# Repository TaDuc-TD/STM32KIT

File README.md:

# STM32F401 Development Board

Bo mạch phát triển tùy chỉnh sử dụng vi điều khiển STM32F401, được thiết kế bằng phần mềm KiCad.

---

## 1. Tổng quan PCB

### Mô hình PCB 3D

### Ảnh bo mạch thực tế

---

## 2. Mô tả dự án

Dự án tập trung vào thiết kế sơ đồ nguyên lý (schematic) và thiết kế mạch in (PCB) cho một bo mạch phát triển dựa trên vi điều khiển STM32F401.

Bo mạch được phát triển nhằm phục vụ cho việc nghiên cứu hệ thống nhúng, phát triển firmware, giao tiếp ngoại vi, thử nghiệm phần cứng và xây dựng các ứng dụng điều khiển sử dụng vi điều khiển.

---

## 3. Tính năng chính

- Thiết kế schematic và PCB hoàn toàn tùy chỉnh.
- Sử dụng vi điều khiển dòng STM32F401.
- Thiết kế và đi dây PCB bằng KiCad.
- Kiểm tra mô hình 3D để đánh giá bố trí linh kiện và khả năng lắp ráp cơ khí.

---

## 4. Thông số phần cứng

| Thông số | Giá trị |
| :--- | :--- |
| **Vi điều khiển** | STM32F401 Series |
| **Phần mềm thiết kế** | KiCad (Schematic Editor, PCB Editor, 3D Viewer) |
| **Nguồn cấp** | 5V DC |
| **Kích thước PCB** | 100 mm × 100 mm |
| **Số lớp PCB** | 2 lớp |
| **Giao tiếp ngoại vi** | 1× RS232 (MAX3232), 1× RS485 (MAX3485), 1× Ethernet (W5500) |
| **I/O & Ngoại vi khác** | 2× ADC, 4× Button, 5× LED |

---

## 5. Quy trình thiết kế

1. Thiết kế sơ đồ nguyên lý (Schematic).
2. Lựa chọn linh kiện và gán footprint.
3. Bố trí linh kiện và đi dây PCB.
4. Kiểm tra quy tắc thiết kế (DRC).

---

## 6. Công cụ sử dụng

- **KiCad**: Thiết kế nguyên lý, PCB, quản lý footprint và kiểm tra mô hình 3D.
- **Git**: Quản lý phiên bản mã nguồn cục bộ.
- **GitHub**: Lưu trữ mã nguồn và tài liệu dự án trực tuyến.

---

## 7. Cấu trúc Repository

```text
├── *.kicad_pro    # Tệp cấu hình dự án KiCad
├── *.kicad_sch    # Thiết kế sơ đồ nguyên lý
├── *.kicad_pcb    # Thiết kế mạch in PCB
└── images/        # Hình ảnh thực tế và ảnh render 3D

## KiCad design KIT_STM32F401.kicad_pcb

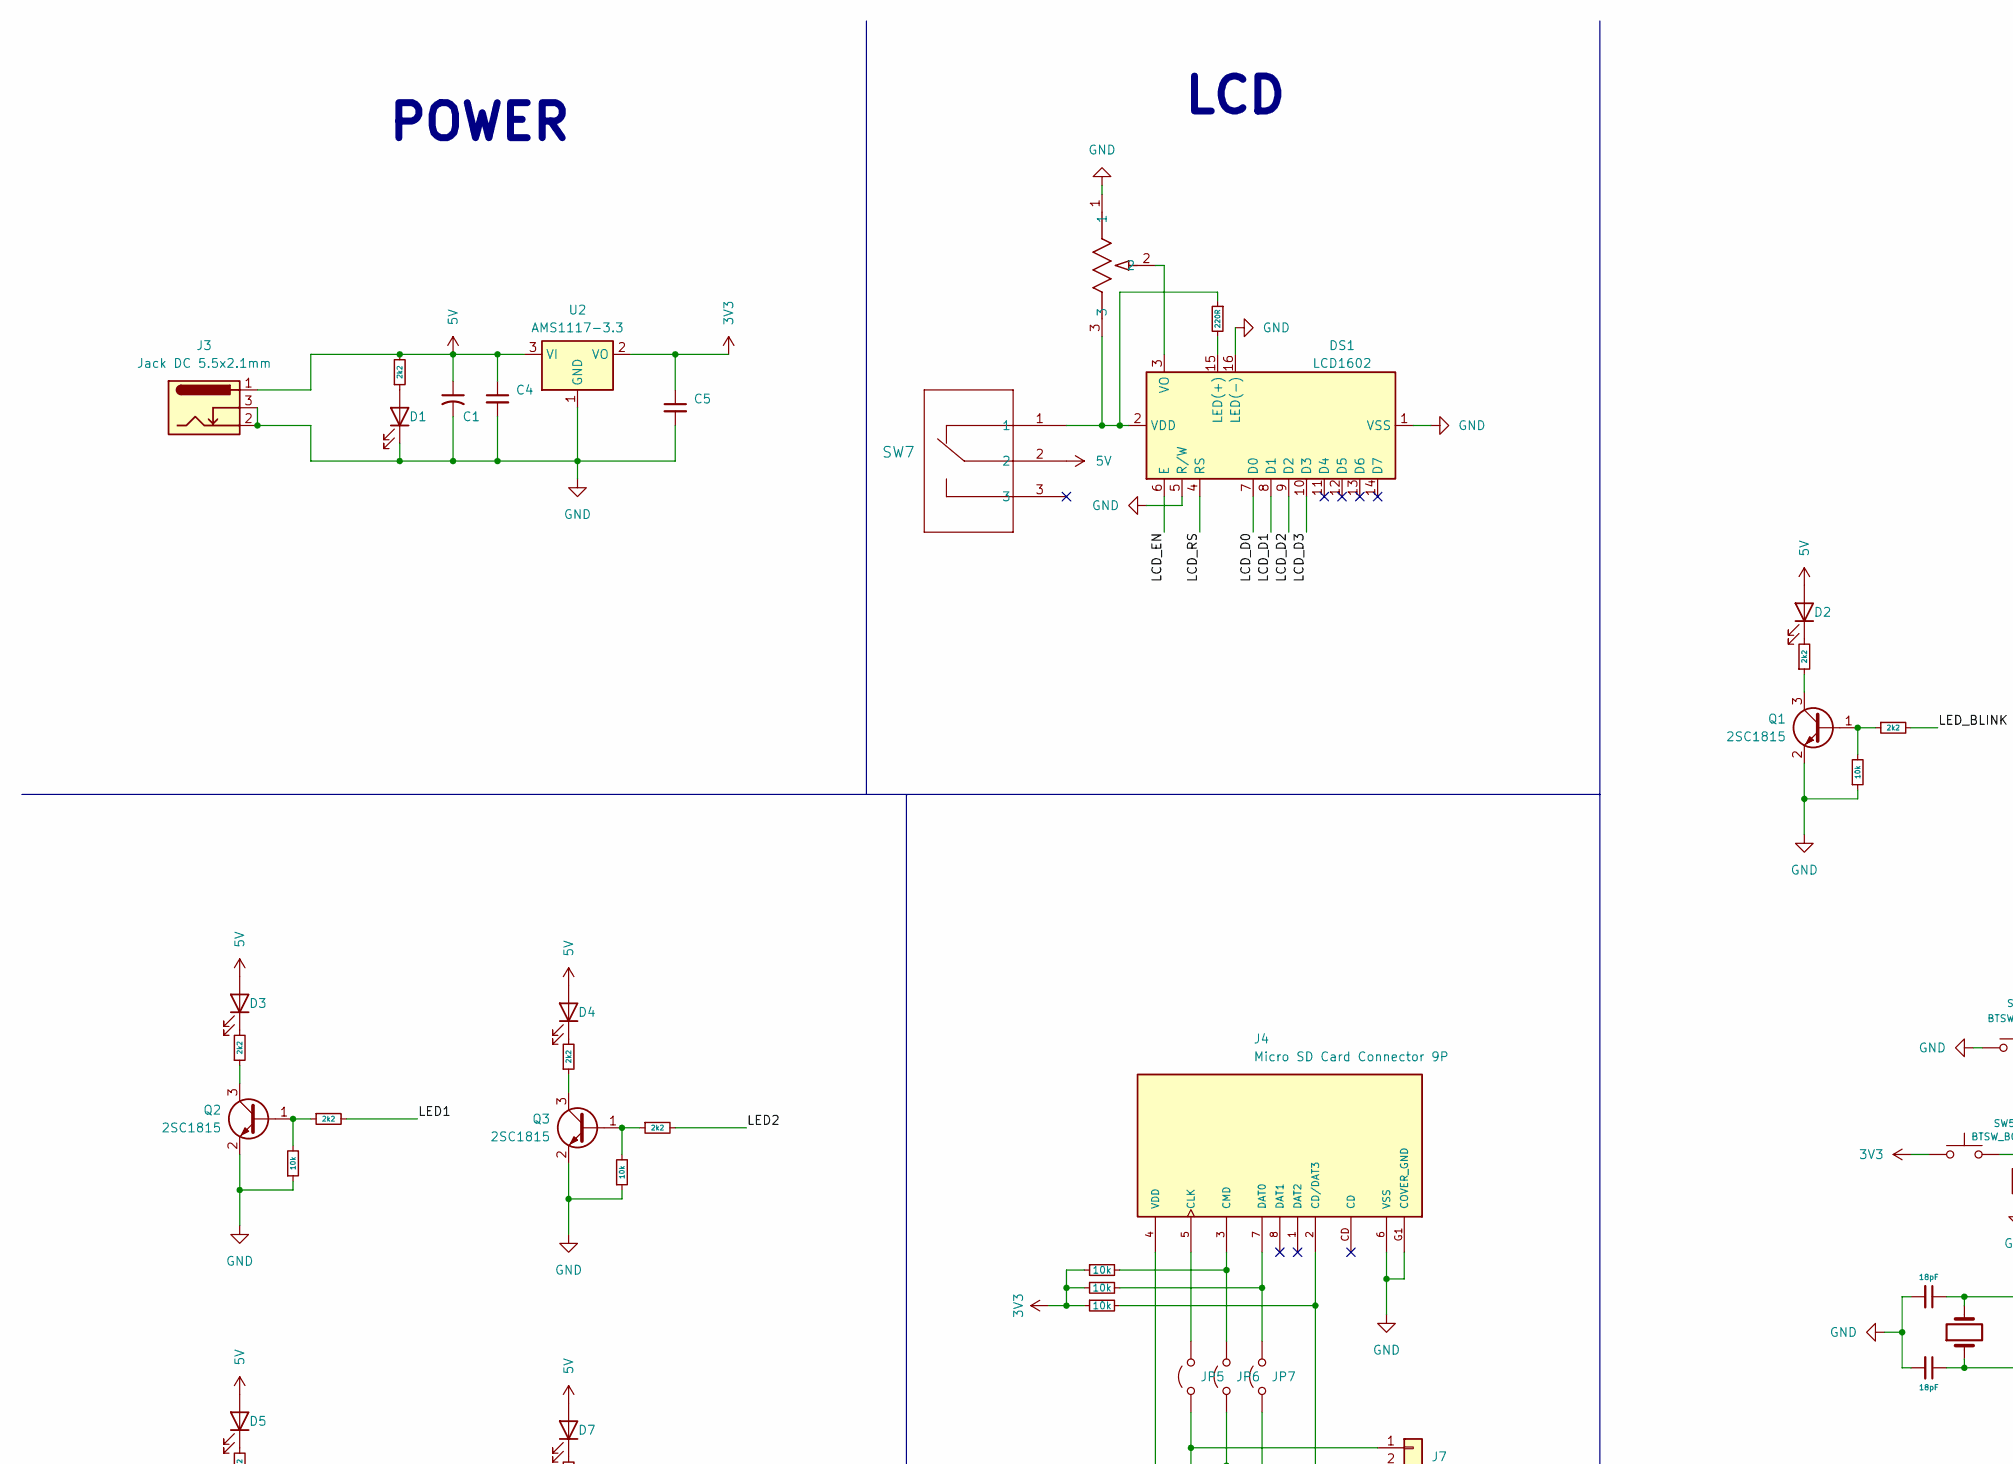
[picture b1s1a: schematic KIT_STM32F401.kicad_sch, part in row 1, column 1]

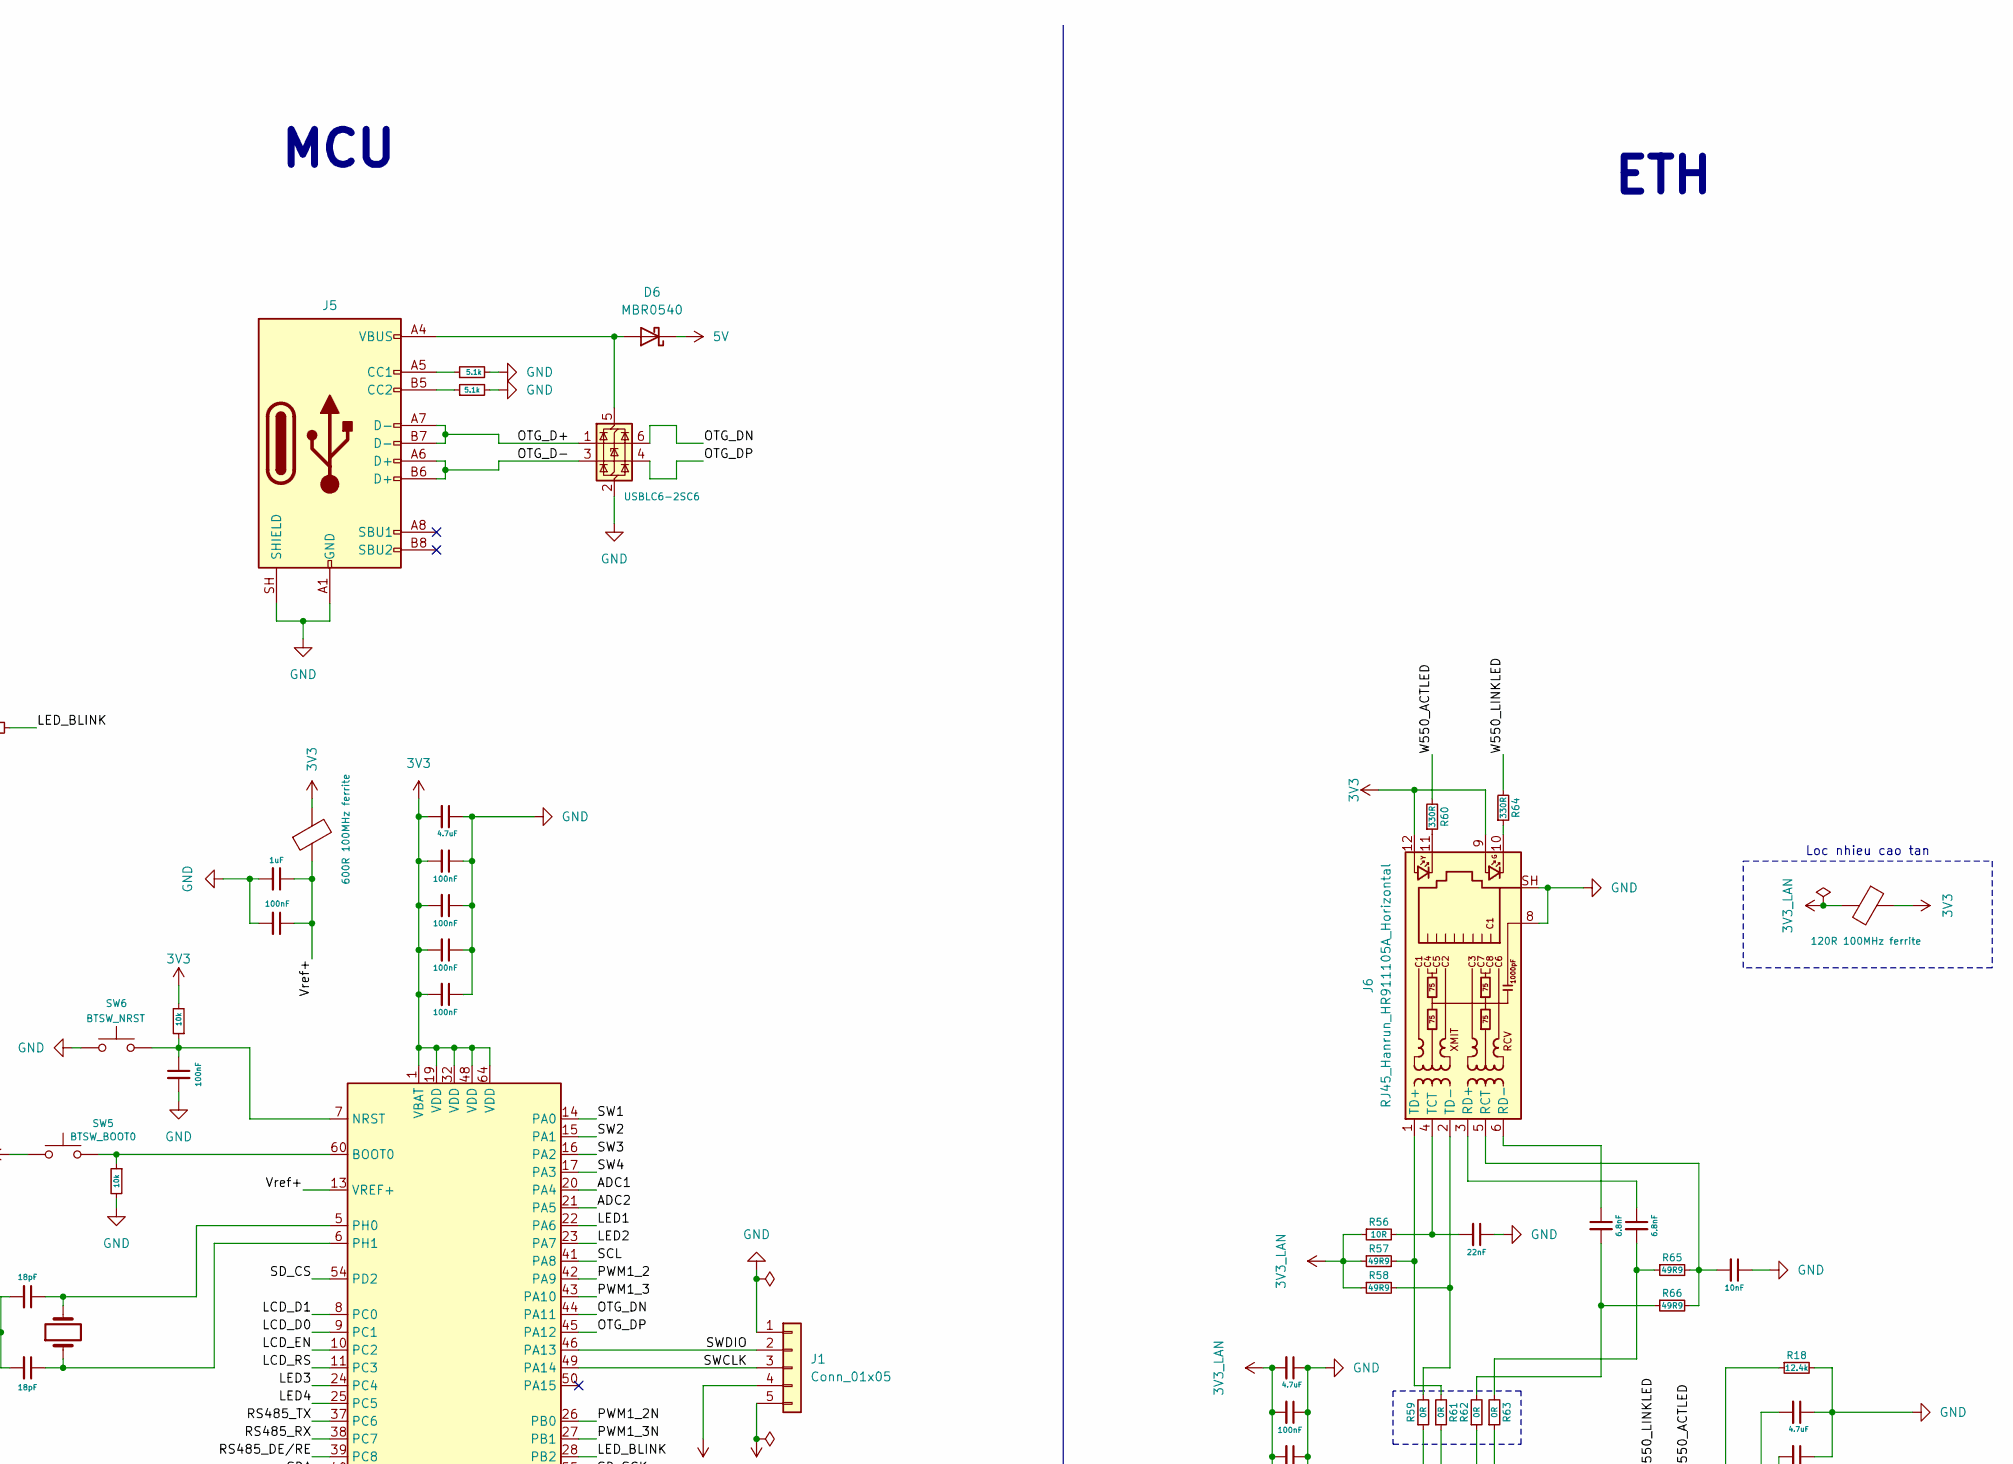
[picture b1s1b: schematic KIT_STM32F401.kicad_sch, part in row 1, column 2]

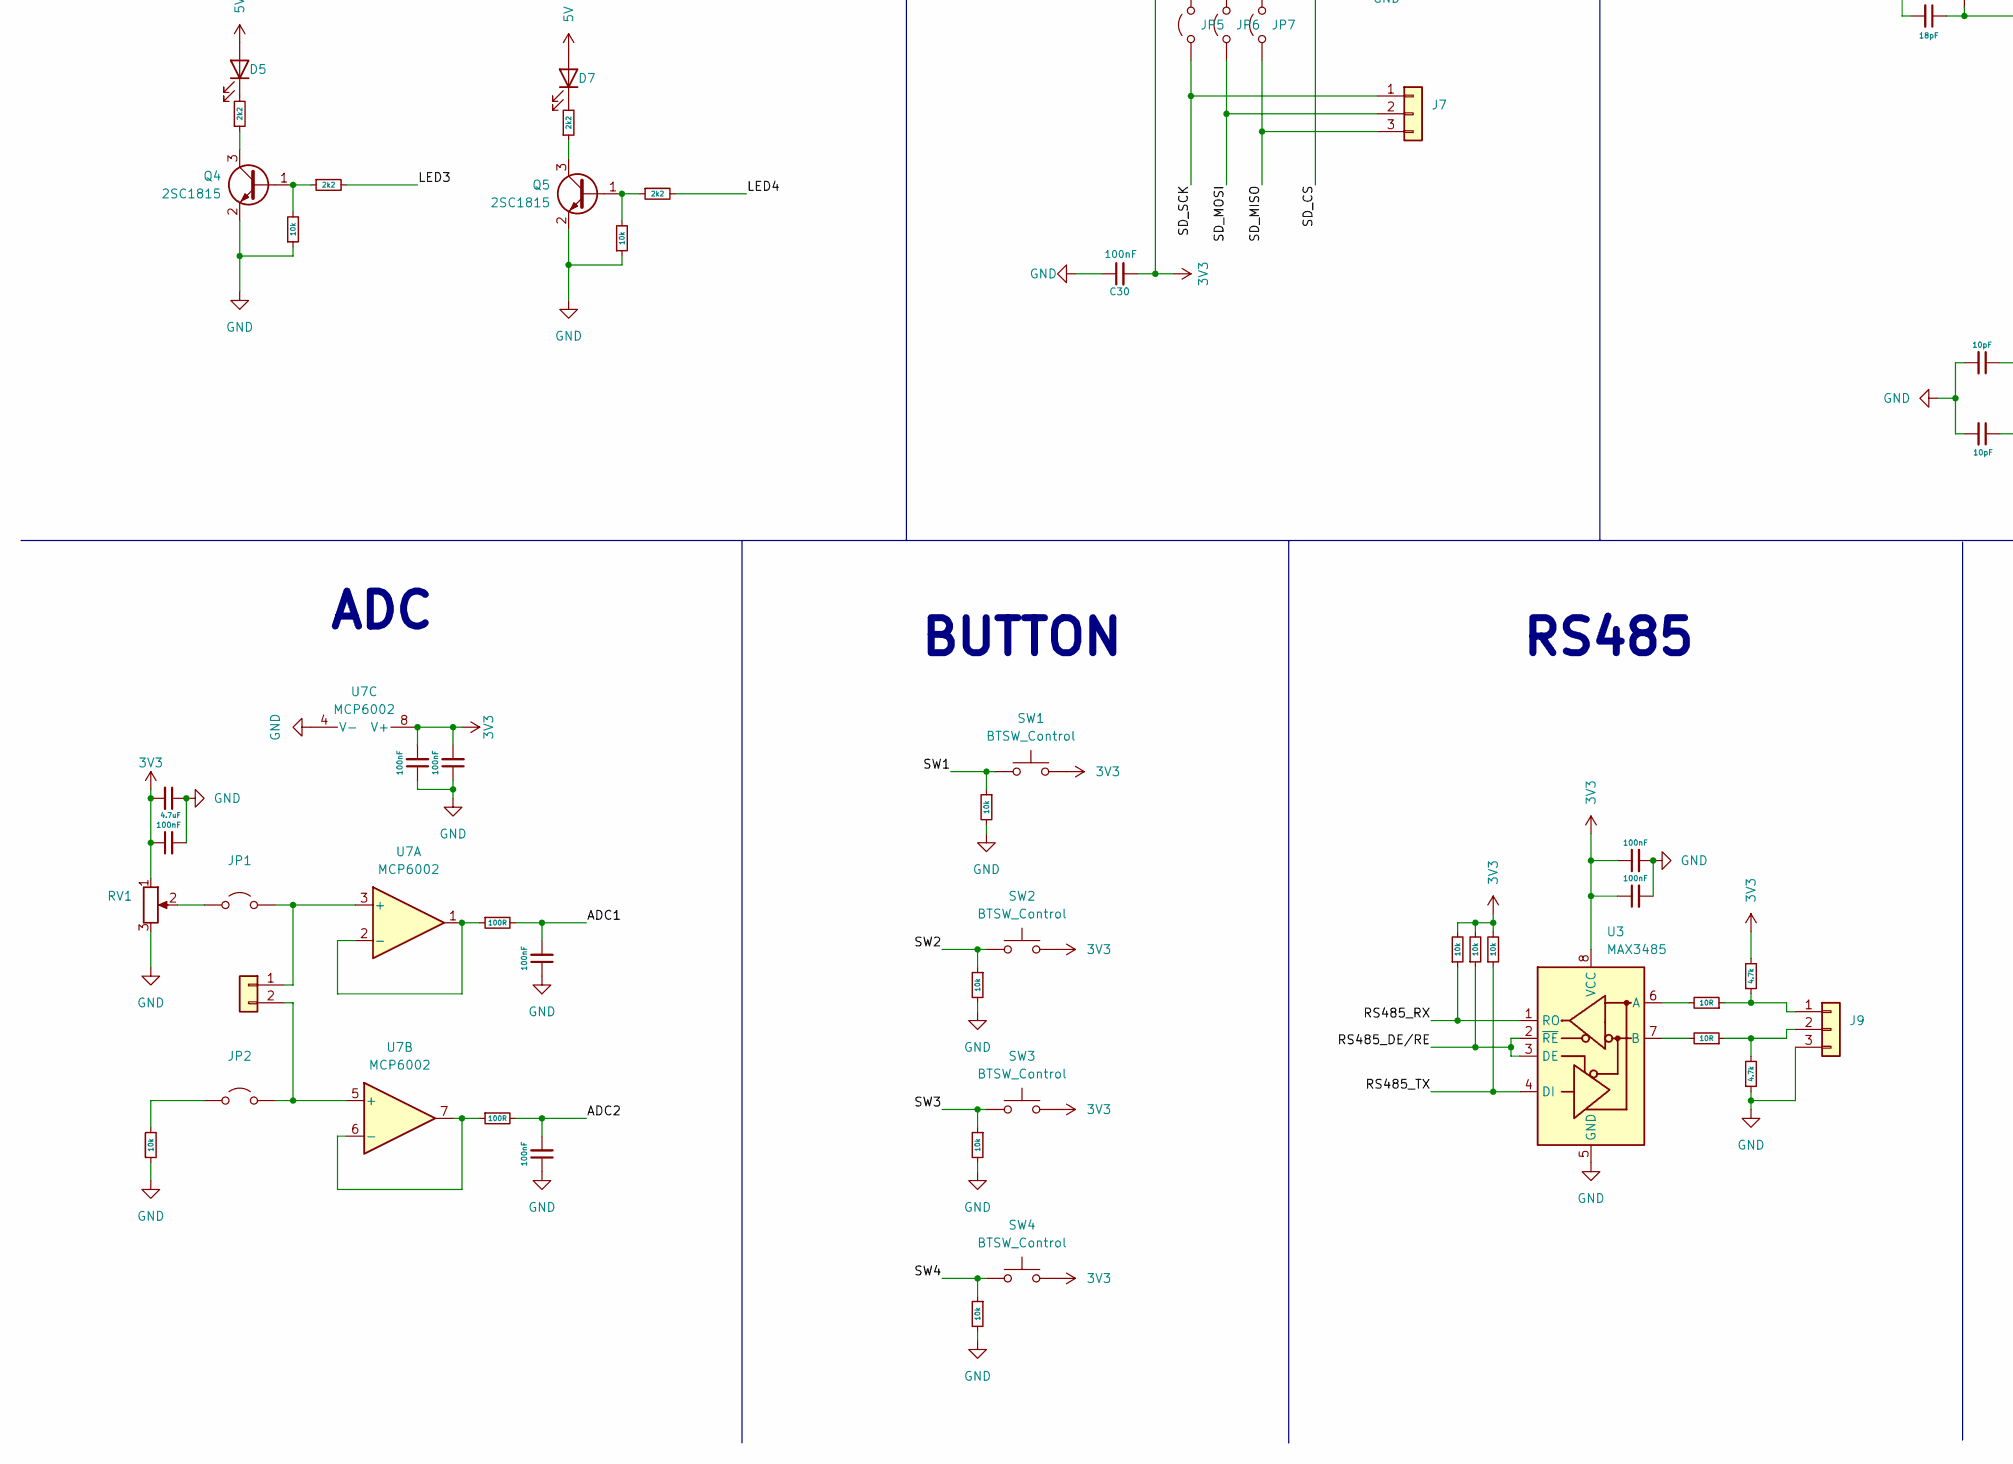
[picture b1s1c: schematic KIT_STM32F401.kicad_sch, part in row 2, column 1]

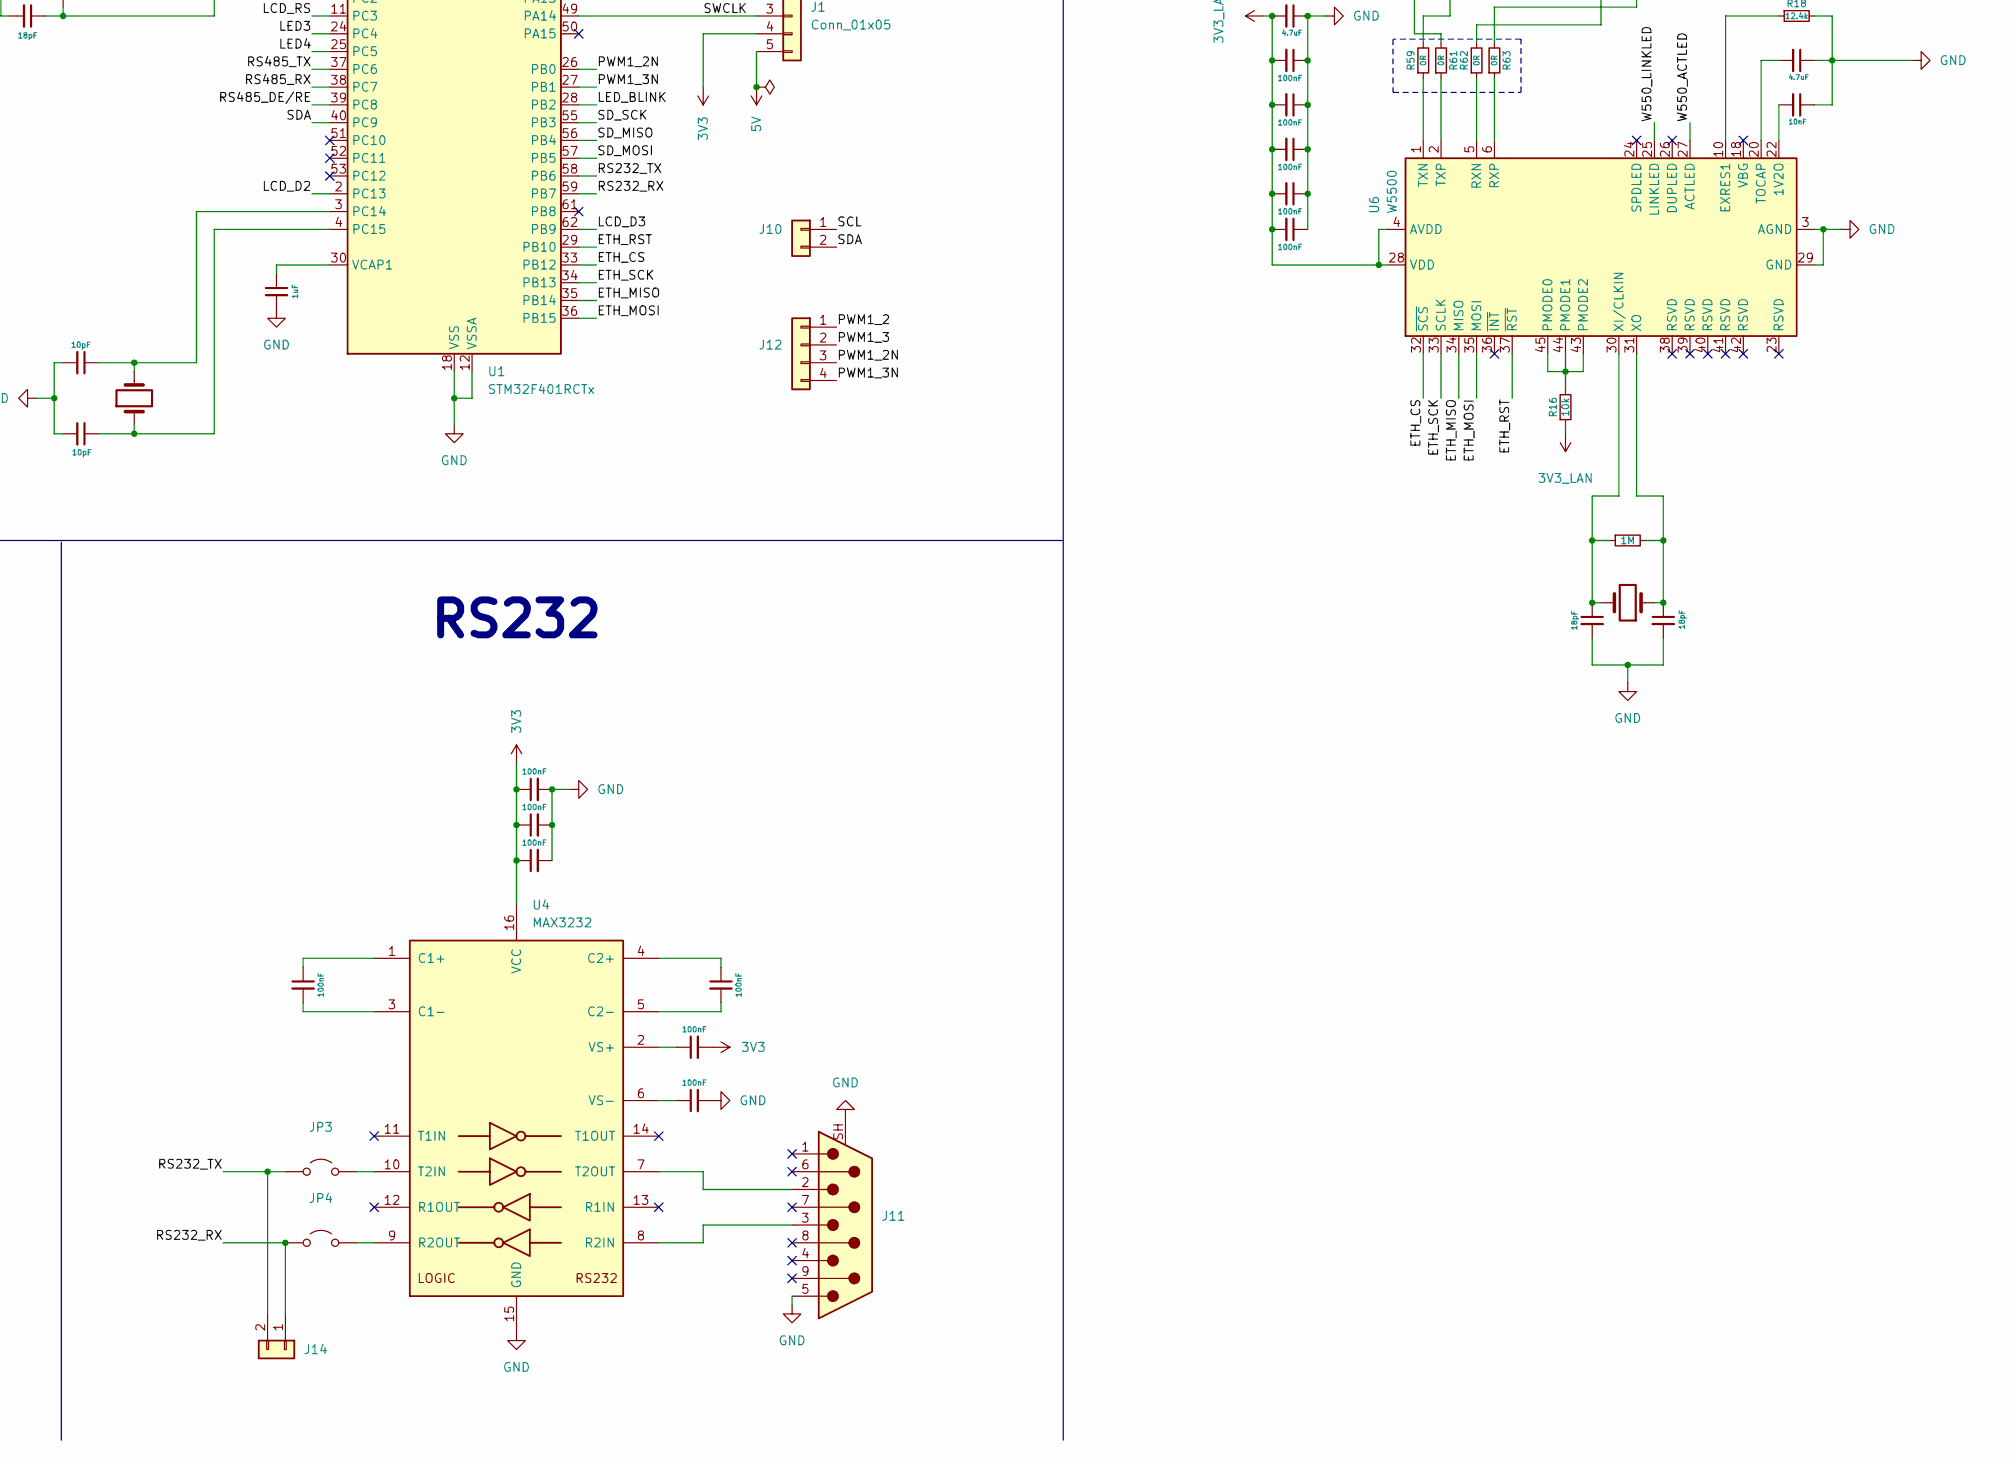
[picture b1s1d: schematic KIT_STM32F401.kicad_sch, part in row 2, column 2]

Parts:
C1: 220uF; CP_Elec_10x10
C4, C30, C33, C35, C36, C37, C38, C39, C42, C43, C44, C45, C46, C47, C48, C49, C50, C51, C52, C53, C54, C56, C57, C58, C59, C69, C70: 100nF; C_0603_1608Metric
C5, C34, C55, C67, C71: 4.7uF; C_1206_3216Metric
C24, C25, C62, C65: 18pF; C_0603_1608Metric
C31, C32: 10pF; C_0603_1608Metric
C40, C41: 1uF; C_1206_3216Metric
C61: 22nF; C_0603_1608Metric
C63, C64: 6.8nF; C_0603_1608Metric
C66, C68: 10nF; C_0603_1608Metric
D1, D2, D3, D4, D5, D7: LED; LED_1206_3216Metric
D6: MBR0540; D_SOD-123
DS1: LCD1602; WC1602A
FB2: 600R 100MHz ferrite; L_0603_1608Metric
FB3: 120R 100MHz ferrite; L_0603_1608Metric
J1: Conn_01x05; PinHeader_1x05_P2.54mm_Vertical
J3: Jack DC 5.5x2.1mm; BarrelJack_GCT_DCJ200-10-A_Horizontal
J4: Micro SD Card Connector 9P; CUI_MSD-4-A; PARTREV 1.0
J5: USB_C_USB2.0_16P; USB_C_Receptacle_GCT_USB4105-xx-A_16P_TopMnt_Horizontal
J6: RJ45_Hanrun_HR911105A_Horizontal
J7: Conn_01x03; PinHeader_1x03_P2.54mm_Vertical
J8: Conn_01x02; PhoenixContact_MSTBA_2,5_2-G-5,08_1x02_P5.08mm_Horizontal
J9: Conn_01x03; PhoenixContact_MSTBA_2,5_3-G-5,08_1x03_P5.08mm_Horizontal
J10, J14: Conn_01x02; PinHeader_1x02_P2.54mm_Vertical
J11: DE9_Connecter_RS232; DSUB-9_Socket_Horizontal_P2.77x2.84mm_EdgePinOffset7.70mm_H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
J12: Conn_01x04; PinHeader_1x04_P2.54mm_Vertical
JP1, JP2, JP3, JP4, JP5, JP6, JP7: Jump 01x02; PinHeader_1x02_P2.54mm_Vertical
Q1, Q2, Q3, Q4, Q5: 2SC1815; TSOT-23
R1: Biến trở vuông 10k; POT_3362P
R10: 1M; R_0603_1608Metric
R16, R22, R23, R24, R25, R26, R29, R30, R31, R36, R39, R41, R42, R45, R48, R51, R54, R89, R90: 10k; R_0603_1608Metric
R18: 12.4k; R_0603_1608Metric
R20, R21: 5.1k; R_0603_1608Metric
R27: 220R; R_0603_1608Metric
R28, R37, R38, R44, R46, R47, R49, R50, R52, R53, R55: 2k2; R_0603_1608Metric
R32, R33: 4.7k; R_0603_1608Metric
R34, R35, R56: 10R; R_0603_1608Metric
R40, R43: 100R; R_0603_1608Metric
R57, R58, R65, R66: 49R9; R_0603_1608Metric
R59, R61, R62, R63: 0R; R_0603_1608Metric
R60, R64: 330R; R_0603_1608Metric
RV1: Biến trở 10k RK097; Potentiometer_Alps_RK097_Single_Horizontal
SW1, SW2, SW3, SW4: BTSW_Control; SW_Push_1P1T_NO_E-Switch_TL3301NxxxxxG
SW5: BTSW_BOOT0; SW_SPST_TS-1088-xR025
SW6: BTSW_NRST; SW_SPST_TS-1088-xR025
SW7: SW-SS12D00; 1P2T_SS-12D00_CNK
U1: STM32F401RCTx; LQFP-64_10x10mm_P0.5mm
U2: AMS1117-3.3; SOT-223-3_TabPin2
U3: MAX3485; SOIC-8_3.9x4.9mm_P1.27mm
U4: MAX3232; SOP-16_4.4x10.4mm_P1.27mm
U5: USBLC6-2SC6; SOT-23-6
U6: W5500; LQFP-48_7x7mm_P0.5mm
U7: MCP6002; SOIC-8_3.9x4.9mm_P1.27mm
Y3: 25MHz; Crystal_SMD_HC49-SD
Y4: 32.768k; Crystal_C38-LF_D3.0mm_L8.0mm_Vertical
Y5: 32.768k; Crystal_SMD_HC49-SD

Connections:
3V3: C5.1, C30.2, C34.2, C35.2, C36.2, C37.2, C38.2, C44.1, C45.1, C46.1, C47.2, C49.1, C50.1, C51.2, C52.2, C70.1, C71.2, FB2.2, FB3.1, J1.4, J4.4 (VDD), J6.9, J6.12, R23.2, R29.2, R30.2, R31.2, R32.2, R42.1, R89.1, R90.1, RV1.1, SW1.2, SW2.2, SW3.2, SW4.2, SW5.2, U1.1 (VBAT), U1.19 (VDD), U1.32 (VDD), U1.48 (VDD), U1.64 (VDD), U2.2 (VO), U3.8 (VCC), U4.16 (VCC), U7.8 (V+); also elsewhere on the board
3V3_LAN: C55.2, C56.2, C57.2, C58.2, C59.2, C69.2, FB3.2, R16.1, R56.1, R57.1, R58.1, U6.4 (AVDD), U6.8 (AVDD), U6.11 (AVDD), U6.15 (AVDD), U6.17 (AVDD), U6.21 (AVDD), U6.28 (VDD)
5V: C1.1, C4.1, D2.2 (A), D3.2 (A), D4.2 (A), D5.2 (A), D6.1 (K), D7.2 (A), J1.5, J3.1, R28.2, SW7.2, U2.3 (VI)
/ADC1: C53.2, R40.2, U1.20 (PA4)
/ADC2: C54.2, R43.2, U1.21 (PA5)
/ETH_CS: U1.33 (PB12), U6.32 (~SCS)
/ETH_MISO: U1.35 (PB14), U6.34 (MISO)
/ETH_MOSI: U1.36 (PB15), U6.35 (MOSI)
/ETH_RST: U1.29 (PB10), U6.37 (~RST)
/ETH_SCK: U1.34 (PB13), U6.33 (SCLK)
/LCD_D0: DS1.7 (D0), U1.9 (PC1)
/LCD_D1: DS1.8 (D1), U1.8 (PC0)
/LCD_D2: DS1.9 (D2), U1.2 (PC13)
/LCD_D3: DS1.10 (D3), U1.62 (PB9)
/LCD_EN: DS1.6 (E), U1.10 (PC2)
/LCD_RS: DS1.4 (RS), U1.11 (PC3)
/LED1: R46.2, U1.22 (PA6)
/LED2: R49.2, U1.23 (PA7)
/LED3: R52.2, U1.24 (PC4)
/LED4: R55.2, U1.25 (PC5)
/LED_BLINK: R37.2, U1.28 (PB2)
/OTG_D+: J5.A7 (D-), J5.B7 (D-), U5.1 (I/O1)
/OTG_D-: J5.A6 (D+), J5.B6 (D+), U5.3 (I/O2)
/OTG_DN: U1.44 (PA11), U5.6 (I/O1)
/OTG_DP: U1.45 (PA12), U5.4 (I/O2)
/PWM1_2: J12.1, U1.42 (PA9)
/PWM1_2N: J12.3, U1.26 (PB0)
/PWM1_3: J12.2, U1.43 (PA10)
/PWM1_3N: J12.4, U1.27 (PB1)
/RS232_RX: J14.1, JP4.1 (A), U1.59 (PB7)
/RS232_TX: J14.2, JP3.1 (A), U1.58 (PB6)
/RS485_DE/RE: R30.1, U1.39 (PC8), U3.2 (~RE), U3.3 (DE)
/RS485_RX: R31.1, U1.38 (PC7), U3.1 (RO)
/RS485_TX: R29.1, U1.37 (PC6), U3.4 (DI)
/SCL: J10.1, U1.41 (PA8)
/SDA: J10.2, U1.40 (PC9)
/SD_CS: J4.2 (CD/DAT3), R90.2, U1.54 (PD2)
/SD_MISO: J7.3, JP7.1 (A), U1.56 (PB4)
/SD_MOSI: J7.2, JP6.1 (A), U1.57 (PB5)
/SD_SCK: J7.1, JP5.1 (A), U1.55 (PB3)
/SW1: R24.1, SW1.1, U1.14 (PA0)
/SW2: R25.1, SW2.1, U1.15 (PA1)
/SW3: R26.1, SW3.1, U1.16 (PA2)
/SW4: R36.1, SW4.1, U1.17 (PA3)
/SWCLK: J1.3, U1.49 (PA14)
/SWDIO: J1.2, U1.46 (PA13)
/Vref+: C39.1, C40.1, FB2.1, U1.13 (VREF+)
/W550_ACTLED: R60.2, U6.27 (ACTLED)
/W550_LINKLED: R64.2, U6.25 (LINKLED)
GND: C1.2, C4.2, C5.2, C24.2, C25.2, C30.1, C31.2, C32.2, C33.2, C34.1, C35.1, C36.1, C37.1, C38.1, C39.2, C40.2, C41.2, C44.2, C45.2, C46.2, C48.2, C49.2, C50.2, C51.1, C52.1, C53.1, C54.1, C55.1, C56.1, C57.1, C58.1, C59.1, C61.1, C62.2, C65.2, C66.1, C67.1, C68.1, C69.1, C70.2, C71.1, D1.1 (K), DS1.1 (VSS), DS1.5 (R/W), DS1.16 (LED(-)), J1.1, J3.2, J3.3, J4.6 (VSS), J4.G1 (COVER_GND), J4.G2 (COVER_GND), J4.G3 (COVER_GND), J4.G4 (COVER_GND), J5.A1 (GND), J5.A12 (GND), J5.B1 (GND), J5.B12 (GND), J5.SH (SHIELD), J6.8, J6.SH, J9.3, J11.5, J11.SH (PAD), Q1.2 (E), Q2.2 (E), Q3.2 (E), Q4.2 (E), Q5.2 (E), R1.1, R18.2, R20.2, R21.2, R22.2, R24.2, R25.2, R26.2, R33.1, R36.2, R39.1, R41.1, R45.1, R48.1, R51.1, R54.1, RV1.3, SW6.1, U1.12 (VSSA), U1.18 (VSS), U1.31 (VSS), U1.47 (VSS), U1.63 (VSS), U2.1 (GND), U3.5 (GND), U4.15 (GND), U5.2 (GND), U6.3 (AGND), U6.9 (AGND), U6.14 (AGND), U6.16 (AGND), U6.19 (AGND), U6.29 (GND), U6.48 (AGND), U7.4 (V-); also elsewhere on the board
unnamed: C63.2, R62.2, R66.1
unnamed: C64.2, R63.2, R65.1
unnamed: D1.2 (A), R28.1
unnamed: D2.1 (K), R38.2
unnamed: D3.1 (K), R44.2
unnamed: D4.1 (K), R47.2
unnamed: D5.1 (K), R50.2
unnamed: D6.2 (A), J5.A4 (VBUS), J5.A9 (VBUS), J5.B4 (VBUS), J5.B9 (VBUS), U5.5 (VBUS)
unnamed: D7.1 (K), R53.2
unnamed: DS1.15 (LED(+)), R27.2
unnamed: DS1.2 (VDD), R1.3, R27.1, SW7.1
unnamed: DS1.3 (VO), R1.2
unnamed: J4.5 (CLK), JP5.2 (B)
unnamed: J4.3 (CMD), JP6.2 (B), R42.2
unnamed: J4.7 (DAT0), JP7.2 (B), R89.2
unnamed: J5.A5 (CC1), R20.1
unnamed: J5.B5 (CC2), R21.1
unnamed: J6.10, R64.1
unnamed: J6.11, R60.1
unnamed: C66.2, J6.5 (RCT), R65.2, R66.2
unnamed: C64.1, J6.3 (RD+)
unnamed: C63.1, J6.6 (RD-)
unnamed: C61.2, J6.4 (TCT), R56.2
unnamed: J6.1 (TD+), R57.2, R61.2
unnamed: J6.2 (TD-), R58.2, R59.2
unnamed: J8.1, JP1.2 (B), U7.3 (+)
unnamed: J8.2, JP2.2 (B), U7.5 (+)
unnamed: J9.1, R32.1, R34.1
unnamed: J9.2, R33.2, R35.1
unnamed: JP1.1 (A), RV1.2
unnamed: JP2.1 (A), R41.2
unnamed: JP3.2 (B), U4.10 (T2IN)
unnamed: JP4.2 (B), U4.9 (R2OUT)
unnamed: Q1.1 (B), R37.1, R39.2
unnamed: Q1.3 (C), R38.1
unnamed: Q2.1 (B), R45.2, R46.1
unnamed: Q2.3 (C), R44.1
unnamed: Q3.1 (B), R48.2, R49.1
unnamed: Q3.3 (C), R47.1
unnamed: Q4.1 (B), R51.2, R52.1
unnamed: Q4.3 (C), R50.1
unnamed: Q5.1 (B), R54.2, R55.1
unnamed: Q5.3 (C), R53.1
unnamed: R22.1, SW5.1, U1.60 (BOOT0)
unnamed: C33.1, R23.1, SW6.2, U1.7 (NRST)
unnamed: C31.1, U1.3 (PC14), Y4.2
unnamed: C32.1, U1.4 (PC15), Y4.1
unnamed: C24.1, U1.5 (PH0), Y5.2
unnamed: C25.1, U1.6 (PH1), Y5.1
unnamed: C41.1, U1.30 (VCAP1)
unnamed: R34.2, U3.6 (A)
unnamed: R35.2, U3.7 (B)
unnamed: C42.1, U4.1 (C1+)
unnamed: C42.2, U4.3 (C1-)
unnamed: C43.1, U4.4 (C2+)
unnamed: C43.2, U4.5 (C2-)
unnamed: J11.3, U4.8 (R2IN)
unnamed: J11.2, U4.7 (T2OUT)
unnamed: C47.1, U4.2 (VS+)
unnamed: C48.1, U4.6 (VS-)
unnamed: C68.2, U6.22 (1V2O)
unnamed: R18.1, U6.10 (EXRES1)
unnamed: R16.2, U6.43 (PMODE2), U6.44 (PMODE1), U6.45 (PMODE0)
unnamed: R62.1, U6.5 (RXN)
unnamed: R63.1, U6.6 (RXP)
unnamed: C67.2, U6.20 (TOCAP)
unnamed: R59.1, U6.1 (TXN)
unnamed: R61.1, U6.2 (TXP)
unnamed: C62.1, R10.1, U6.30 (XI/CLKIN), Y3.2
unnamed: C65.1, R10.2, U6.31 (XO), Y3.1
unnamed: R40.1, U7.1, U7.2 (-)
unnamed: R43.1, U7.6 (-), U7.7

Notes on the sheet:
ETH
RS485
LCD
Loc nhieu cao tan
BUTTON
MCU
ADC
POWER
RS232

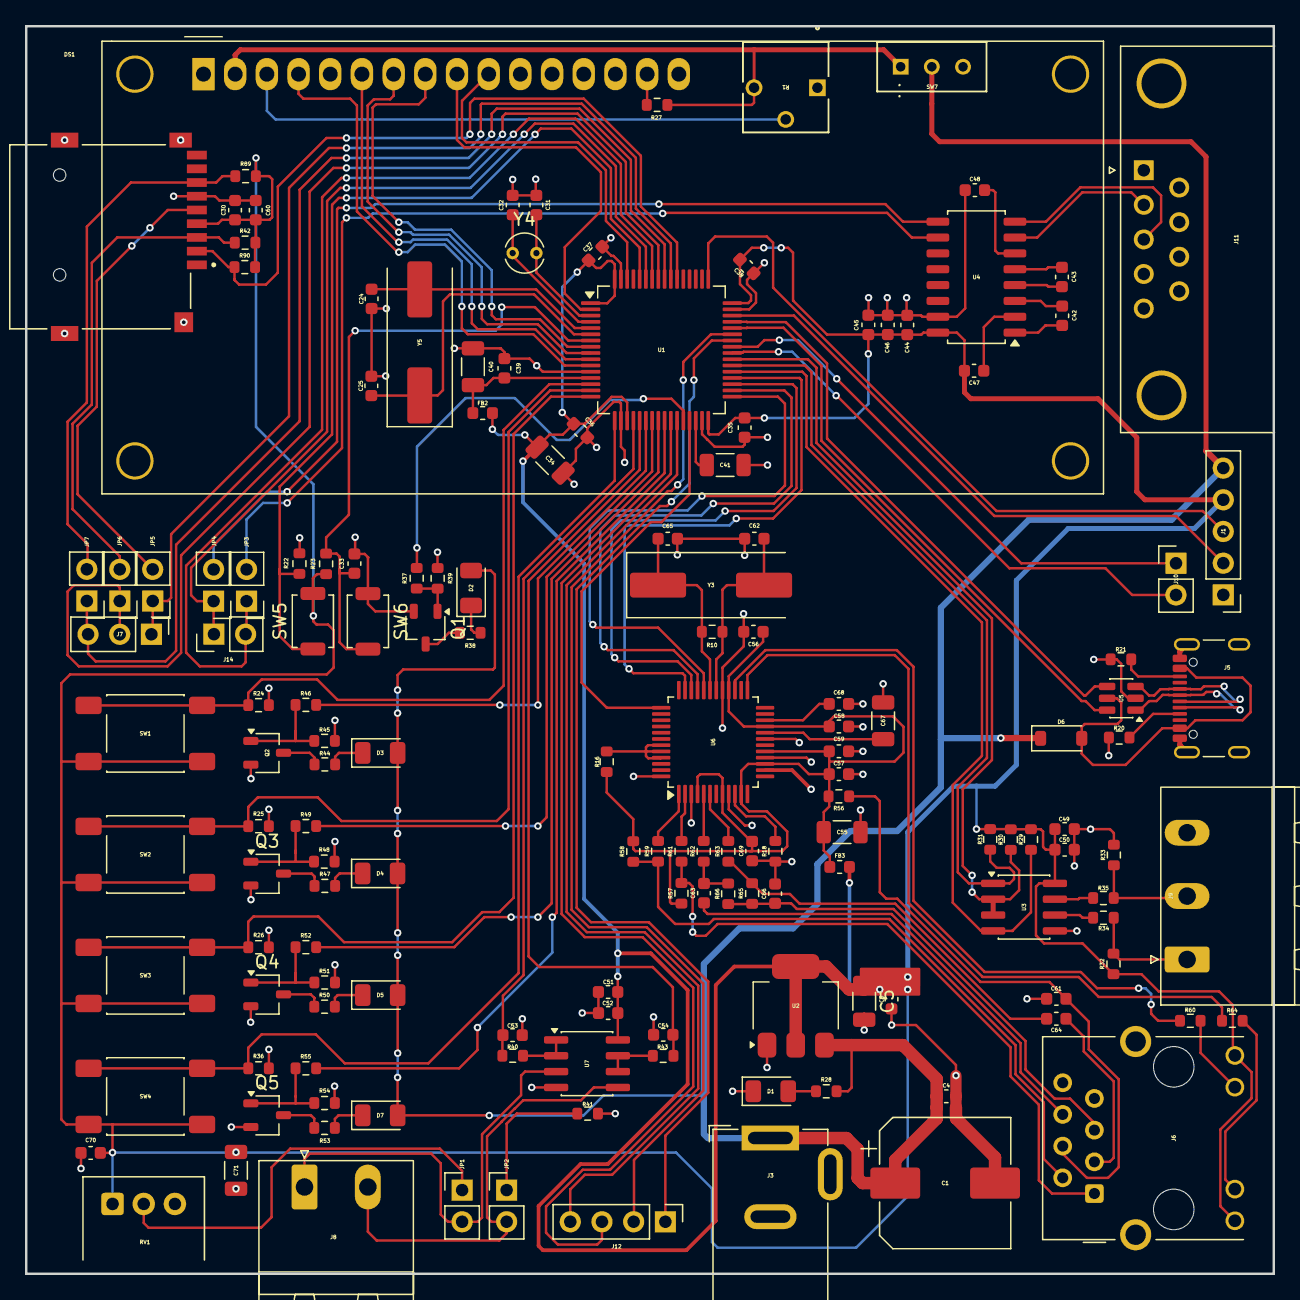
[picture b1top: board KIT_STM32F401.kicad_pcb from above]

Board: 2 copper layers, 100.0 x 100.0 mm, 153 parts (0 on the bottom side), 122 nets.

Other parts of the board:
C5#2: C_Small; C_0603_1608Metric
C60: 10uF; C_0603_1608Metric

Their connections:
3V3: C5#2.1, C60.2; also elsewhere on the board
GND: C5#2.2, C60.1; also elsewhere on the board
